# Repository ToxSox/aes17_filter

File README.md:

# AES17 class-D measurement filter

A passive low-pass that sits between a class-D amplifier and an audio analyzer, so that the
amplifier's switching residue never reaches the analyzer's input stage. It is the circuit of
the Audio Precision AUX-0025, on a 158 × 124 mm board in a Hammond 1444-862 aluminium chassis
with every connector in its front long wall, with the 20 kHz knee trimmable, a 20:1 pad that a 4PDT toggle switches on or takes off entirely, and the
AUX-0025's own connectors: female XLR and dual banana in, male XLR out. Designed for a QuantAsylum QA403, usable with
anything that has a 100 kΩ input.

**Status: designed, simulated, generated, not yet built - a prototype, not yet a reference.**
The Gerbers and the JLCPCB files are in `hardware/fab/`, checked against each other by
`hardware/check_release.py`; the first five boards were ordered in November 2026 and have not
been built or measured yet. Everything below the
simulation line is therefore a claim, not a measurement. The design review's
[verification plan](docs/design-review.md#verification-what-makes-it-a-reference) lists what has
to pass before it counts as a reference: the ferrite coils' linearity first, then the ground with
bridged amplifiers, heat, and the stop band.

## Where this comes from

This repository is a fork of Matt Clark's
[aes17_filter_25](https://github.com/mattclarkdotnet/aes17_filter_25) (V2, May 2024), itself a
DIY copy of the AUX-0025, released under the CERN-OHL-W 2.0. The V2 KiCad project, Gerbers,
case cut-outs and dissipation spreadsheet were removed from this tree because they no longer
describe this board; they are intact in the history, on the branch **`v2-mattclark`** (the GitHub proxy of this session refused to push a tag, so it is a branch). The licence
stays the CERN-OHL-W 2.0 (`LICENSE.txt`), and the source location of this derived design is
https://github.com/ToxSox/aes17_filter.

What changed against V2, and why, is argued at length in
[docs/design-review.md](docs/design-review.md), which also takes up the three changes the V2
README had planned (shielded coils: first yes, then no after a second review - see below; a 60 V
goal: no gain; an SMD version: dearer for small runs). In short:

| | V2 (mattclarkdotnet) | this fork | why |
|---|---|---|---|
| Input resistor | 500 Ω 5 W fixed | AP's network: 1 kΩ 3 W ‖ 14 kΩ ‖ (1 kΩ 3 W + 500 Ω trimmer) | the trimmer sets the 20 kHz knee; V2 sits at +0.10 dB and spreads to 0.21 dB with 5 % coils, trimmed boards land at ±0.03 dB whatever the parts |
| Filter values | E24 approximations (330 Ω + 440 pF, 68 Ω, 3.3 kΩ, 22 Ω) | the AUX-0025's own (412 Ω + 2 × 220 pF, 75 Ω, 3.40 kΩ, 24.9 Ω), all E96 | 1-2 dB more in the stop band, nothing to lose |
| Pad | 9 kΩ / 1 kΩ, two poles per leg, hand-wired toggle | 2 × 10 kΩ / 1 kΩ, all 0.1 % / 15 ppm (about 21.8:1), two poles per leg on a 4PDT toggle (gold contacts): in DIRECT the pad is off the output and the filter sees the analyzer alone, as on the AUX-0025. | the QA403 clips at 40 Vrms and loses 20 dB of floor above its +18 dBV range; 20:1 keeps a 2 kW amplifier below both. 0.1 % in every arm because the QA403 subtracts the legs in its analogue input: 1 % arms would let −36 dB of common mode through |
| Connectors | XLR in and out, banana test points | the AUX-0025's: female XLR plus a dual-banana pair and a common in, male XLR out, through the chassis' front wall | one set of cables tests this filter and an AUX-0025 alike; a QA403 hangs on an XLR-to-two-BNC lead |
| Board | 175 × 90 mm, four layers | 158 × 124 mm, four layers, generated from a data file; all connectors on the front long edge; whole ground planes, 0.8 mm clearance, pad and switch at the output connector, one chassis bond at the input | the filter hangs with its connectors towards the operator, as the AUX-0025's front panel; the layout rules are in [hardware/README.md](hardware/README.md#layout-rules-it-follows) |
| Rating | "140 Vrms continuous" | a curve, per leg to ground: 75 Vrms to 15 kHz (the pad), 55 Vrms at 20 kHz (the trimmer's current), 30 Vrms from 30 kHz to 1 MHz (trimmer, then the 0.6 W resistors around the coils); several tones at once (audio over a class-D carrier) share it: the sum of (V / Vmax)² stays at or below 1 | at 20 kHz the shunt capacitors draw current through the input network: V2's single resistor takes 13 W at 140 V, and this build's trimmer reaches its rating at 56 V; above 70 kHz the stop band's current flows in R4 and R6 |
| Coils | Würth 7687480102, unshielded ±5 % | the same Würth 7687480102 | the most linear ferrite coil of the size, and the tightest; the shielded WE-TIS fits the same footprint for comparison |
| Assembly | hand-built | JLCPCB for everything it has in stock (22 parts per board); coils, film capacitors, the two 412 Ω and the Cliff sockets bought locally and soldered by hand | JLCPCB had those only on pre-order (19-21 working days); the trimmer absorbs the tolerances in the frequency response; pairing coils **and** capacitors between the legs to 1 % gains 14 dB of common-mode rejection at 20-100 kHz (one of the two alone 2-4 dB) |

## What is in the tree

| Path | What |
|---|---|
| [docs/design-review.md](docs/design-review.md) | the review of the V2 design against the AUX-0025 and the QA403, the simulation, the pad decision, the build decisions, the bill of materials, grounding with bridged amplifiers, the verification plan, safety |
| [docs/sourcing.md](docs/sourcing.md) | the shopping list with hard specifications, substitutes and open questions |
| [sim/aes17_sim.py](sim/aes17_sim.py) | the AC analysis that produced every number in the review (numpy only) |
| [hardware/](hardware/) | `design.py` (parts and nets as data), `make_pcb.py` (places, routes and checks the board with KiCad's `pcbnew`), `export.py` (Gerbers, BOM, placement), the schematic, the front-wall drilling, and [hardware/README.md](hardware/README.md) with the ordering steps |
| [hardware/fab/](hardware/fab/) | `aes17-filter-gerbers.zip`, `aes17-filter-bom.csv`, `aes17-filter-cpl.csv` for JLCPCB; `aes17-filter-parts.csv` with notes |

## Simulated performance

One leg against ground, 100 kΩ load, relative to 1 kHz; the script prints the full tables.

| | V2 as published | this fork, trimmed |
|---|---|---|
| Passband 20 Hz - 20 kHz | −0.00 / +0.10 dB nominal, up to 0.21 dB spread with ±5 % coils | within ±0.03 dB after trimming, whatever the coils and capacitors |
| −3 dB | 58 kHz | 58 kHz |
| 250 kHz | −53.6 dB | −52.5 dB (two 220 pF instead of 390 pF) |
| 500 kHz | −57.5 dB | −58.4 dB |
| 1 MHz | −69 dB | −70 dB |
| Insertion loss | −0.05 dB | −0.05 dB direct (the pad is switched off) |
| Common mode in the difference, 95 % of boards | - | −74 dB at 50 Hz direct, −52 dB through the pad, −31 dB at 20 kHz; −45 dB with coils and capacitors paired |
| Source noise at the analyzer | −124 dBV direct | −124 dBV direct, −122 dBV through the pad |
| Input resistor at 63 Vrms, 20 kHz | 2.7 W | 1.4 W in each of two |

A real box will land a few decibels short of the stop-band figures: one V1 build measured 45 dB
at 248 kHz against 55 simulated, and the 1 mH coils' self-resonance (1.3 MHz) takes 10-20 dB off
above 2 MHz, where the filter is 80 dB down anyway.

## Bill of materials, per board

The generated list is `hardware/fab/aes17-filter-bom.csv`; this is the same in words. Prices
are LCSC or JLCPCB's global-sourcing quote on 1 November 2026, single quantity.

| Qty | Part | For | Source | ≈ |
|---|---|---|---|---|
| 4 | **Würth WE-TI HV 7687480102**, 1 mH ±5 %, unshielded, 1.0 Ω, 0.8 A, 400 V | L1-L4 | **soldered by hand**, not in the JLCPCB order: Digi-Key (285 in stock at 1.61 € on 1 November 2026); the 120 V 7447480102 is the same coil (JLCPCB C1331132, pre-order). The shielded WE-TIS 7447471102 (C1331105) fits the same footprint and is the comparison for the linearity test; JLCPCB lists it as ±20 %, which the trimmer cannot always reach. Trimmed boards with the ±5 % coil land within 0.032 dB and need R1 between 495 and 534 Ω, inside the network's 483-575 Ω | 2.1 € |
| 4 | UNI-ROYAL MFR03SF1001A10, 1.00 kΩ 1 % 3 W 50 ppm | input network | C58750 | $0.06 |
| 2 | 14.0 kΩ 1 % 0.25 W | input network | C127223 | $0.01 |
| 2 | Bourns 3296W-1-501LF, 500 Ω 25-turn trimmer | 20 kHz knee | C69564 | $0.97 |
| 6 | WIMA FKP2J002201D00HSSD, 220 pF 630 V ±2.5 % | C1, C5, and the bypass pairs C2+C9, C6+C10 (440 pF) | **soldered by hand**, not in the JLCPCB order: Bürklin (also as FKP2J002201D00ESSD, ±1 %, 42D8516); LCSC C5742108 would be pre-order | $0.23 |
| 4 | WIMA FKP2F014701I00JA00, 4.7 nF 250 V ±5 % | C3, C4, C7, C8 | **soldered by hand**, not in the JLCPCB order: Digi-Key (0.67 €); LCSC C20412818 would be pre-order | $0.41 |
| 2 | 412 Ω 1 % **0.6 W**, Vishay MRS25000C4120FCT00 | bypass across L1; carries the stop band above 150 kHz | **soldered by hand**: any 412 Ω 1 % 0.6 W in a 0207 body (Vishay MRS25 / MBB0207, Yageo MF0207) from Digi-Key, Mouser or Bürklin; JLCPCB C1235858 had three in stock | - |
| 2 | 75.0 Ω 1 % 1 W, CCO MF1W | between the stages | C160685 | $0.05 |
| 2 | 3.40 kΩ 1 % **0.6 W**, Vishay MRS25000C3401FCT00 | across L3; carries the current near 100 kHz | C1366835 | - |
| 2 | 24.9 Ω 1 % 0.25 W, Yageo MFR-25FBF52-24R9 | output | C3542579 | $0.03 |
| 4 | TE YR1B10KCC, 10.0 kΩ **0.1 % 15 ppm** 0.25 W | pad, upper arms (2 × 10 kΩ over 1 kΩ, about 21.8:1); the same family as the lower arm | C1364313, in stock | $0.50 |
| 2 | TE YR1B1K0CC, 1.00 kΩ 0.1 % | pad, lower arm | C1364308 | $0.50 |
| 1 | Neutrik NC3FAAH2, female XLR, horizontal PCB | J4, input (pin 2 +, pin 3 −) | C368522, in stock | $0.84-1.80 |
| 1 | Neutrik NC3MAAH, male XLR, horizontal PCB | J5, output (pin 2 +, pin 3 −) | C368463, in stock | $0.79-1.80 |
| 3 | Cliff FCR7350 R / B / G, 4 mm safety sockets, at 19.05 mm for a dual banana plug | J1-J3 | **soldered by hand**, not in the JLCPCB order: Digi-Key, 6.80 € (JLCPCB: pre-order at $11-12) | 7 € |

Not on the board, per board: four screws for the XLR flanges (M3 as the front-wall drawing has
them; check Neutrik's drawing whether the NC3FAAH2 / NC3MAAH flange takes M3 or a 2.9 mm
self-tapping screw), one **4PDT** ON-ON non-shorting toggle with **gold contacts** and a 1/4 in
bushing, such as the APEM 5666CDB (its ten wires go into W1's holes; the switch carries
microamperes, a dry circuit), one Hammond 1444-862 chassis
with its 1434-86 bottom plate and seven 10 mm M3 spacers, the one under the plated hole H5 metal; and once for the bench a lead from the
amplifier terminals to a male XLR plug (or dual banana leads) and an XLR-female-to-two-BNC lead
for the QA403, both of which an AUX-0025 takes as well.

## Ordering and building

[hardware/README.md](hardware/README.md): upload the three files in `hardware/fab/` to JLCPCB,
five boards, all five assembled, Economic. The JLCPCB files hold only parts JLCPCB had in stock, so
the assembly waits for nothing. Everything it had only on pre-order is left out and bought in
Germany (Bürklin, Digi-Key): the ten WIMA capacitors, the four coils, the two 412 Ω and the three
Cliff sockets. They are soldered by hand after assembly, about 55 joints per board; the
capacitors and coils measured and paired between the legs first if an LCR meter is at hand. Then drill the front wall after
`hardware/aes17-filter-frontwall.png`, trim both legs through an amplifier until 20 kHz equals
1 kHz, measure both ratios (PAD about 21.8:1, DIRECT about 1.006:1), and enter them in the
measurement software as the probes' ratios.

## Before connecting it

- **DIRECT passes DC.** A single-supply bridged amplifier idles at half its supply on both
  terminals (+24 V on a 48 V TPA3255); in DIRECT that adds to the signal's peak at the QA403,
  whose absolute maximum is 56 Vpk including DC. With such an amplifier, or an unknown one, use
  PAD, and switch with the amplifier off.
- **It is a class-D pre-filter, not the AES17 low-pass itself**, and it wants a source of a few
  ohms: a line-level output with 50-100 Ω per leg loses 0.3-0.6 dB at 20 kHz through it.
- **The rating is per leg and falls with frequency** (75 / 55 / 30 Vrms, see the table above);
  full-power sweeps above 20 kHz and filterless amplifiers' carriers are what reach it.

## Licence

CERN Open Hardware Licence Version 2 - Weakly Reciprocal, as the original. Copyright of the
original design Matt Clark 2023-2024; the changes described above and in the design review were
made in November 2026 in this repository. If you build or change it, the licence asks that you
keep these notices and make your changes available under the same terms.

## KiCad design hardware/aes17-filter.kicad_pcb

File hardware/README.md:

# AES17 filter board: files and how to order

The passive class-D measurement filter from [docs/design-review.md](../docs/design-review.md),
as a board. Everything here is generated from `design.py`; nothing was drawn by hand, so a
changed value or part is a changed line and a re-run.

| File | What it is |
|---|---|
| `design.py` | every part with value, footprint, LCSC number and note; every net |
| `make_pcb.py` | places and routes the board with KiCad 7's `pcbnew` module, fills the ground planes, runs the DRC; writes `aes17-filter.kicad_pcb` |
| `export.py` | writes `fab/`: the Gerber + drill zip, the JLCPCB bill of materials and placement file, a parts list with notes |
| `make_schematic.py` | draws `aes17-filter-schematic.svg/.png` (schemdraw) |
| `make_frontwall.py` | draws the front wall's drilling and the panel legend, `aes17-filter-frontwall.svg/.png` |
| `check_release.py` | checks that the board, the order files, the source hash and the DRC report belong together; exit code 0 = fit to order |
| `aes17-filter.kicad_pcb` | the board, for KiCad 7 or newer; there is no `.kicad_sch`, the schematic is the drawing |
| `fab/aes17-filter-gerbers.zip` | upload this to JLCPCB |
| `fab/aes17-filter-bom.csv` | upload this as the BOM (Comment, Designator, Footprint, LCSC Part #) |
| `fab/aes17-filter-cpl.csv` | upload this as the placement file (Designator, Mid X, Mid Y, Layer, Rotation) |
| `fab/aes17-filter-parts.csv` | the same parts with values and notes, for ordering anything elsewhere |
| `fab/aes17-filter-schematic.pdf`, `fab/aes17-filter-drc.txt` | the schematic and the DRC report of this release |
| `fab/RELEASE.txt` | title, revision, the source hash printed on the board, and the SHA-256 of every order file |

## The board

158 × 124 mm, four layers, 1.6 mm, in a **Hammond 1444-862** aluminium chassis (203 × 152 × 51 mm,
flat 1 mm walls, closed by the 1434-86 bottom plate). **Every connector is on the front long
edge** and comes through the chassis' front long wall, so the filter hangs with that wall towards
the operator, as the AUX-0025's front panel does. From the left, seen from the front: the female
XLR input (pin 2 +, pin 3 −, pin 1 and shell ground), red and black 4 mm sockets at AP's
19.05 mm for a dual banana plug, the green common, the male XLR output (pin 2 +, pin 3 −), and
the pad toggle, mounted high in the wall straight above the switch. The QA403 is fed through a
self-made lead, XLR female to two BNC males. The first 24 mm behind the front edge are the
connector strip with the switch and the pad block at its right-hand end; the filter is the
100 mm band behind it, the two legs mirror images about its centre line. Layers 2 and 3 are
whole ground planes, broken only by the holes; every track is on layer 1 or 4. The board stands
on seven M3 spacers on the bottom plate (four on the centre line, H5 in the connector strip,
H6 and H7 in the back corners); the XLRs are screwed to the wall, the Cliff sockets held
by the board alone (they have no panel retention; the wall just has a clearance hole for the
Ø11 barrel). The DRC in KiCad 7 reports no errors and no unconnected nets at 0.8 mm clearance;
the warnings are silkscreen over pads and the footprints not being from a library table.

### Layout rules it follows

The board was gone over once more with the usual rules for audio layout. What they changed:

- **Whole ground planes.** Layers 2 and 3 carry nothing but ground. The earlier layout ran the
  two filter outputs on layer 3, which cut slots into the plane right under the output tracks
  on layer 4; those tracks lost their return path exactly where the analyzer's signal ran.
- **Clearance for the voltage.** Everything from the input up to OUT (in the direct position)
  carries the amplifier's voltage: laid out for 120 V peak (85 Vrms per leg, above the 75 Vrms rating). IPC-2221B asks 0.8 mm
  between bare pads at 101-300 V; the board had 0.3 mm and now keeps 0.8 mm everywhere. The
  male XLR's lands on pins 1 and 2 are 3.0 mm instead of Neutrik's 3.4 mm for the same reason.
- **The pad and the switch at the output connector.** The two pads now stand side by side right
  behind the switch, identical copies, so they share a temperature and their ratios track. The
  4PDT toggle sits in the wall straight above W1, ten solder holes, and its wires drop about
  15 mm into them; before, they ran 75 mm through the box to a header in the middle of the
  board. W1's holes run in the order the nets leave the pad block (OUT, F, F, PT, PAD), the +
  leg's row on top and the − leg's on the bottom, so no track crosses another; the − leg's tracks
  come down between the + row's holes, 5.08 mm apart for exactly that.
- **Long runs only at low impedance.** The negative leg ends at the back of the board, so one
  track has to come forward. It is now the filter output F_N, behind 24.9 Ω, the lowest
  impedance in the chain, and it runs alone through empty board. Before, the output pair came
  back to the middle of the board, and in the pad position OUT sits behind 950 Ω, where 1 pF of
  stray capacitance from the input side is already −50 dB at 500 kHz.
- **Pairs kept together.** IN+ and IN− run on top of each other (layer 1 over layer 4) from the
  connectors to where the legs part; OUT+ and OUT− run side by side, 1 mm apart, from W1 to the
  XLR. Before, the negative input went round the board's left edge and the two outputs ran 10 mm
  apart.
- **More distance between the stages.** The second coil of each leg is 38 mm from the first
  instead of 32 mm. Coupling between two drum cores falls with the cube of the distance, so
  L1 → L2, the one path that bypasses the filter, is about 4.5 dB weaker.
- **One chassis bond, where the cables come in.** H5 is a plated hole on ground in the
  connector strip, next to the input XLR: with a metal spacer it ties the ground plane to the
  bottom plate and so to the chassis, and cable shield currents go to the chassis there instead
  of crossing the filter. The other six holes are plain.

What stayed as it was, because it was right: the two legs mirror images, so each sees the same
parasitics; the shunt capacitors' grounds meeting in the middle of the board, so the
differential residue current takes a short path between the legs; polypropylene capacitors and
metal-film resistors throughout; the hot 3 W input resistors well away from the polypropylene
capacitors (FKP2 is rated to 100 °C).

### Silkscreen

Top: every part with its name and value in the notation that survives a lost dot (R1 1k 3W,
R7 24R9, C3 4n7, L1 1mH), the pad block with a legend under each pad, each leg's signal flow
along its outer edge (input network, stage 1, stage 2, pad), a high-voltage warning beside the
inputs, W1's ten holes labelled for the toggle wires (+OUT, +F, +F, +PT, +PAD and the same with −), and the title
"AES17 filter rev A" with date, licence and source location (the CERN-OHL-W asks for the source
location on the product where practicable). Bottom, readable from below: a crib sheet with the
connector pin-outs and the QA403 lead, the switch wiring, the trim procedure and
the voltage limits. Both sides carry "src" and the source hash, the first seven digits of the
SHA-256 of `design.py` and `make_pcb.py`, the same as in `fab/RELEASE.txt`. Two ground loops,
TP1 and TP2, sit between the stages for a scope probe's ground spring. Title, revision and date
are three constants at the top of `design.py`.

## Ordering at JLCPCB

0. **Check the release.** `python3 hardware/check_release.py` must end with "fit to order".
   Order from a commit, not from a working copy, and keep its source hash (in `fab/RELEASE.txt`
   and printed on both sides of the board, "src ...") with the order: a board in the hand is
   then matched to its files without guessing.
1. **PCB.** Upload `fab/aes17-filter-gerbers.zip`. Four layers, 1.6 mm, any colour, 1 oz copper,
   HASL or ENIG as you like, five pieces (the minimum). The stack-up JLCPCB offers for four
   layers (JLC04161H-7628 or similar) is fine; nothing here depends on impedance.
2. **Assembly.** Tick assembly, **five boards** (all of them: two for this bench, two for a
   colleague's, one spare; JLCPCB's minimum is two), top side only, Economic. Upload
   `fab/aes17-filter-bom.csv` and `fab/aes17-filter-cpl.csv`. All parts are through-hole;
   JLCPCB hand-solders those ($3.58 per order plus $0.0164 per joint, one extra day).
3. **Parts review.** In the parts page every line with an LCSC number resolves on its own,
   because the files hold only parts JLCPCB had in stock. **Left out, to be bought locally and
   soldered by hand:** the coils L1-L4 (Würth 7687480102, Digi-Key; at JLCPCB only the
   7447480102, C1331132, on pre-order), the 412 Ω R4/R14, the Cliff sockets J1-J3 and the film
   capacitors C1-C10. The shielded
   WE-TIS 7447471102, C1331105, fits the same footprint; it was the coil of the first draw of
   rev A and is now only the comparison for the linearity test (JLCPCB lists it as ±20 %, which
   the trimmer cannot always reach). The 412 Ω 0.6 W had three pieces in stock at JLCPCB
   (C1235858) on 2 November 2026; any 412 Ω 1 % 0.6 W in a 0207 body does. The
   BOM file is plain ASCII on purpose: JLCPCB's import reads "Würth" as "W眉rth". The ten WIMA film capacitors (C1-C10) are **not in the BOM and the placement file**: JLCPCB has them only on pre-order (19-21 working days, quoted on 3 November 2026), so they are bought locally and soldered by hand. The Cliff sockets would be **pre-order** too: JLCPCB
   buys them after payment, quotes the final price within 48 hours, and they take nine to
   twenty business days to arrive; connectors carry a $20 inspection fee per type, so the three
   Cliff colours cost $60 in inspection alone. So they are **left out of the assembly** (they
   are not in the files), bought at Digi-Key (6.80 € each against $11-12 pre-order) and solder the three per board yourself - one
   pin and four pegs each.
4. **Every line has an LCSC number.** The pad's upper arms (R8, R9, R18, R19) are TE YR1B10KCC,
   10.0 kΩ 0.1 % 15 ppm, C1364313 (2 397 in stock on 2 November 2026), the same family as the
   1.00 kΩ lower arm; a 0207 body on the 15.24 mm pitch. R6/R16 are the Vishay MRS25 3.40 kΩ
   0.6 W, C1366835 (125 in stock).
5. **W1 is not a part.** It is ten plated holes for the toggle's wires and is not in the BOM or
   the placement file; the 4PDT toggle is bought separately (RS, Mouser) and wired by hand.
6. After the order: the five boards arrive assembled. Nothing else is needed from JLCPCB.

### What JLCPCB's BOM tool quoted on 1 November 2026

For an assembly of five boards (quantities include JLCPCB's attrition allowance), in euros:

| Line | Qty | Total | Per piece | Status |
|---|---|---|---|---|
| TE 5227161-7 BNC (C591726) | 20 | 99.63 | 4.98 | in stock; no longer on the board - the XLR output replaced the BNCs |
| Cliff FCR7350R / B / G (C6041087 / C6555263 / C6041085) | 5 each | 58.13 / 58.13 / 50.32 | 11.6 / 11.6 / 10.1 | **shortage: pre-order**, plus the connector inspection fee per type |
| WIMA 220 pF 630 V ±2.5 % (C5742108) | 30 | 7.19 | 0.24 | shortage: pre-order, 19 working days; now soldered by hand instead |
| WIMA 4.7 nF 250 V (C20412818) | 25 | 10.70 | 0.43 | shortage: pre-order, 21 working days; now soldered by hand instead |
| Bourns 3296W-1-501LF (C69564) | 10 | 6.75 | 0.67 | in stock |
| TE YR1B1K0CC 0.1 % (C1364308) | 10 | 3.57 | 0.36 | in stock |
| UNI-ROYAL 1 kΩ 3 W (C58750) | 21 | 1.04 | 0.05 | in stock |
| UNI-ROYAL 10 kΩ 1 W (C58714) | 21 | 0.51 | 0.02 | in stock; replaced by TE YR1B10KCC 0.1 % (C1364313, about 0.50 € each) |
| 75 Ω 1 W (C160685) | 11 | 0.47 | 0.04 | in stock |
| 14 k, 412, 3.4 k, 24.9 (C127223, C3558411, C3517441, C3542579) | 11-15 each | 0.15 / 0.06 / 0.17 / 0.36 | 0.01-0.02 | in stock; the 412 and 3.4 k are now 0.6 W Vishay MRS25 (C1235858, C1366835), not yet quoted |
| Würth 7447471102 coils | 20 | about 58 | 2.9 | "Vorbestellen" → global sourcing; replaced by the unshielded 7447480102 (C1331132, 2.14 €) |

About 356 € of parts for five assembled boards, 71 € per board, of which the three Cliff sockets
are 33 € and the four BNCs 20 € (the BNCs have since left the board). The Cliff sockets are the line to take out of the assembly:
pre-order at 11 € each plus the inspection fee, against 6.80 € at Digi-Key for a part with one
pin and four pegs to solder. That quote still holds the BNCs, the Cliff sockets, the film
capacitors and the coils, none of which is in the JLCPCB files any more; what JLCPCB fits now is
the resistors, the trimmers and the two XLRs, so the parts bill it shows at ordering is well
below it. The stock of all ten lines covered five boards on 3 November 2026; the tightest were
C58750 (1 kΩ 3 W, 153 for 20) and C1366835 (3.40 kΩ, 125 for 10).

## Shopping list, bought locally (five boards)

JLCPCB fits the 22 parts per board it had in stock. Everything else is bought locally; the
quantities are for all five boards and include what pairing the legs needs (see "Building the
boards", step 1). Pair from **one pool for all five**: any matched pair can go on any board.
**Why 24 of a ±5 % part for 20 places:** ten pairs within 1 % are wanted; the chance of finding
them is 21 % from 20 parts, 93 % from 22 and 100 % from 24 if the values spread evenly over the
tolerance, and 42 / 98 / 100 % for a typical reel, whose spread is narrower (simulated,
tolerance = 3σ). Two more cover a bent lead and give the winding-sense test its sender coil.
For a single board it would be 8 for 4 places (98 %), for two boards 12 for 8: the bigger the
pool, the smaller the surplus per board.

**On the board, soldered by hand:**

| Buy | Fitted | Part | Pairing | Where |
|---|---|---|---|---|
| 26 | 20 | **Würth 7687480102**, 1 mH ±5 %, unshielded drum core (L1-L4) | ten pairs, L1/L3 and L2/L4 per board, from 24 | Digi-Key |
| 26 | 20 | **WIMA FKP2F014701I00JA00**, 4.7 nF 250 V ±5 % (C3, C4, C7, C8) | ten pairs, C3/C7 and C4/C8 per board, from 24 | Digi-Key |
| 33 | 30 | **WIMA FKP2J002201D00ESSD**, 220 pF 630 V **±1 %** (C1, C2, C5, C6, C9, C10) | two ±1 % parts differ by 2 % at most, which is what the simulation counts as paired; measure and sort anyway: the closest two as C1/C5, then C2 + C9 against C6 + C10 | Bürklin 42D8516 |
| (40) | (30) | or the ±2.5 % FKP2J002201D00HSSD, if the ±1 % is not to be had | then pairing matters: 40 to choose from | Digi-Key, Bürklin |
| 12 | 10 | **412 Ω 1 % 0.6 W**, Vishay MRS25000C4120FCT00 or any 0207 body (R4, R14) | none needed | Digi-Key, Mouser, Bürklin |
| 5 each | 5 each | **Cliff FCR7350R, FCR7350B, FCR7350G**, red, black, green (J1-J3) | - | Digi-Key, Farnell |

**For pairing and the verification tests, not on the board** (one set does all five boards, if
one person pairs, trims and tests them; that is also how all five come out alike):

| Buy | Part | For |
|---|---|---|
| 1 each | 100 Ω, 6.8 kΩ, 47 kΩ, 1 %, 0.25 W | the series resistor when pairing with the QA403: coils, 4.7 nF, 220 pF |
| 2 + 1 | 10 kΩ and 1 kΩ, 1 %, **3 W or more**, metal film (the UNI-ROYAL MFR03S on the board, or a Vishay PR03) | test 4's reference divider, 2 × 10 k over 1 k as the pad: at 75 Vrms it runs at about 4 % of its rating, so it adds no self-heating distortion of its own |
| 1 | 1 Ω, 1 % | test 5's current shunt in the green lead |
| 4, optional | Würth WE-TIS 7447471102, shielded | test 4's comparison, one board's worth (availability outside JLCPCB not checked) |

Plus the box, the toggle and the leads in the next table.

## What is not on the board

| Qty for five boards | Part | Where |
|---|---|---|
| 20 | screws for the XLR flanges: M3 × 8 and nuts if the flange holes are through-holes, else 2.9 mm self-tapping (Neutrik's drawing of the NC3FAAH2 / NC3MAAH decides; not checked) | any |
| 2 | a cable from the amplifier's terminals to a male XLR plug (pin 2 +, pin 3 −), or dual banana leads - the same cable then feeds an AUX-0025; one per bench | self-made |
| 2 | an XLR-female-to-two-BNC-male lead to the QA403: pin 2 to L+ centre, pin 3 to L− centre, pin 1 to both BNC shells; about 30 cm, both legs equal; one per bench | self-made (Neutrik NC3FXX, two BNC plugs, two pieces of RG58 or RG174) |
| 5 | **4PDT** toggle, ON-ON, non-shorting, **gold contacts**, panel mount, 1/4 in bushing, solder lugs; best with a locking lever | APEM 5666CDB or another 4PDT with gold contacts; the switch carries microamperes at 100 kΩ, a dry circuit, so standard silver contacts (a plain Knitter MTA 206, for one) are not suitable. Gold contacts are rated to switch only 0.4 VA at 20 V: they carry the full voltage closed, but are switched with the amplifier off |
| 5 | insulating sheet, 0.25 mm polyester or fish paper, cut to the bottom plate around the spacers | any |
| 5 | Hammond 1444-862 chassis and 1434-86 bottom plate | Digi-Key, Mouser, Reichelt; about 20 € and 11 € |
| 35 | M3 spacers, 10 mm, and M3 screws, for the board on the bottom plate (seven per board); the one under H5 metal, with a star washer on the bottom plate | any |
| | wire for the toggle: ten pieces per board of about 25 mm, 0.25 mm² stranded, into W1's holes | |

## Building the boards

1. Check the assembled board against `fab/aes17-filter-parts.csv`.
   Then solder what JLCPCB leaves out, per board: the 412 Ω 0.6 W in R4 and R14; the coils,
   L1/L2 (+ leg) and L3/L4 (− leg), all four with the same winding sense (see below); 220 pF in C1, C2, C9 (+) and C5, C6, C10 (−),
   4.7 nF in C3, C4 (+) and C7, C8 (−); and the Cliff sockets, red J1, black J2, green J3. Before
   soldering, **measure coils and capacitors and give the two legs the closest pairs** (L1/L3,
   L2/L4, C1/C5, C2+C9 / C6+C10, C3/C7, C4/C8); the polypropylene parts have no polarity. For
   the frequency response the trimmer takes care of the spread, but not for the legs' phase:
   pairing **both** coils and capacitors to 1 % moves the common mode in the difference from
   −31 to −45 dB at 20 kHz and from −14 to −29 dB at 100 kHz (simulation, 95 % of boards);
   pairing only one of the two gains 2-4 dB, because the other still sets the phase.

   **Pairing without an LCR meter**, with the QA403: its output through a series resistor
   into the part, the part's other end to ground; the left input across the part, the right
   input on the output. Sweep once to find where the left reads 3 dB below the right, then
   read every part of that value at that frequency: 1 % in value is about 0.04 dB there. The
   resistor sets the frequency: 6.8 kΩ for the 4.7 nF (about 5 kHz), 47 kΩ for the 220 pF
   (about 10 kHz with the lead's capacitance), 100 Ω for the 1 mH coils (about 16 kHz). Keep
   the leads and the part's position the same for every part of one value; only the
   differences count.

   **Winding sense of the coils.** For the filter either way round works, but an unshielded
   drum core picks up stray magnetic fields (a mains transformer, a load bank), and the
   aluminium box does not screen 50 Hz. A field that reaches both legs alike then appears as
   common mode, which the QA403 rejects, only if L1 and L3 (and L2 and L4) are the same way
   round; Würth does not mark the start of the winding. To find it with the QA403 before
   soldering: QA403 output, 1 kHz at about 1 V, into one coil (the "sender") through 100 Ω;
   stand each other coil on top of it, axis on axis and always leads up, its leads to the left
   input, and read the phase against the output: about +90° or −90° (the induced voltage leads
   the current). Mark the lead that gives +90° on the left input's centre pin and put it in the
   square pad on all four. Then test the sender itself the same way, with a marked coil as
   the sender.
2. Drill the front wall after `aes17-filter-frontwall.png`; the hole table is at the end of this
   file. Easiest and safest: drill the seven spacer holes in the bottom plate, stand the board on
   its spacers, put the chassis over it, and mark the connector centres through from inside.
3. Fit the board on the bottom plate, put the chassis over it, screw the XLR flanges to the
   wall, fit the toggle.
4. Wire the 4PDT toggle into W1, straight below it, by the silkscreen labels: two poles per
   leg, the + leg to the back row, the − leg to the front row. Decide which lever position is
   PAD and call the throw lugs on that side "PAD side", the others "DIR side"; then per leg
   - pole a: common → PT, PAD side → F, DIR side not connected
   - pole b: common → OUT, PAD side → PAD, DIR side → the other F
   Check with an ohmmeter between the output XLR's pin 2 (then pin 3) and pin 1, inputs open:
   about 1.0 kΩ in PAD (the pad's 1 kΩ leg), open in DIRECT (the pad is off). And from the red
   (then black) input to the green: about 21 kΩ in PAD, open in DIRECT. Mark the positions on the
   front.
5. Lay the insulating sheet on the bottom plate before the board goes in; use a metal spacer
   under H5 and plastic or metal under the rest (only H5 is plated). Set the trimmers (step 6)
   with a few volts from the amplifier: the trim does not depend on the level, and the box is
   open while you turn them.
6. Work through the [verification plan](../docs/design-review.md#verification-what-makes-it-a-reference):
   trim both legs through an amplifier until 20 kHz equals 1 kHz, the pad ratio over frequency
   into the measurement software's probe settings, then the ferrite, ground, heat and stop-band tests before the
   filter is used as a reference. Connect the green socket to the amplifier's ground in use.

## Regenerating

```
python3 hardware/make_pcb.py        # board + DRC report (needs KiCad 7 with pcbnew for Python)
python3 hardware/make_schematic.py  # schematic, also fab/…-schematic.pdf (pip install schemdraw)
python3 hardware/export.py          # fab/ and fab/RELEASE.txt (needs kicad-cli; after the schematic)
python3 hardware/make_frontwall.py  # front wall drilling (matplotlib)
python3 hardware/check_release.py   # do the files belong together?
```

Run `make_schematic.py` before `export.py`: the schematic PDF is one of the files the release
manifest hashes.

## Front wall holes

See `aes17-filter-frontwall.png`; the table below is printed by `make_frontwall.py`. In blue the
drawing also carries the legend for the panel: the rating per leg at the inputs, "GND to the
amplifier ground", the switch positions and DIRECT's 40 Vrms limit. The wall is
the front long wall of the Hammond 1444-862, seen from outside, x from its left end, y from its
bottom edge (which rests on the 1434-86 bottom plate).

| Hole | Ø mm | x | y |
|---|---|---|---|
| XLR IN (female), Neutrik NC3FAAH2 | 22.5 | 40.6 | 24.1 |
| its two M3 screws, upper left and lower right | 3.2 | 30.7 / 50.5 | 34.0 / 14.2 |
| 4 mm IN + (red) | 11.5 | 67.6 | 17.9 |
| 4 mm IN − (black), 19.05 mm from the red one | 11.5 | 86.6 | 17.9 |
| 4 mm GND (green) | 11.5 | 107.6 | 17.9 |
| XLR OUT (male), Neutrik NC3MAAH | 22.5 | 134.6 | 24.1 |
| its two M3 screws, upper left and lower right | 3.2 | 124.7 / 144.5 | 34.0 / 14.2 |
| pad toggle, 1/4 in bushing | 6.4 | 158.6 | 35.6 |

The heights assume the board on **10 mm M3 spacers** on the bottom plate, so its top surface is
11.6 mm above the wall's bottom edge; the Cliff socket axis is 6.3 mm above the board, the XLR
axis 12.5 mm, the toggle's 24 mm (so that the 4PDT's body, about 13 × 17 mm and 20 mm deep with its lugs, clears the board). **The XLR axis height is read off Neutrik's front view, not a dimensioned value:
fit the board on its spacers, hold the undrilled wall against the connector fronts and mark
through before drilling.** The board's front edge sits 3.3 mm behind the wall's inner face, so
the XLR flanges and the shoulders of the 4 mm sockets lie against the wall. Cliff does not
specify a panel hole for the S16N-PC; Ø11.5 clears its Ø11.0 barrel. Neutrik asks for a hole of
at least Ø22 and two Ø3.2 screw holes 19.8 mm apart on the diagonal.

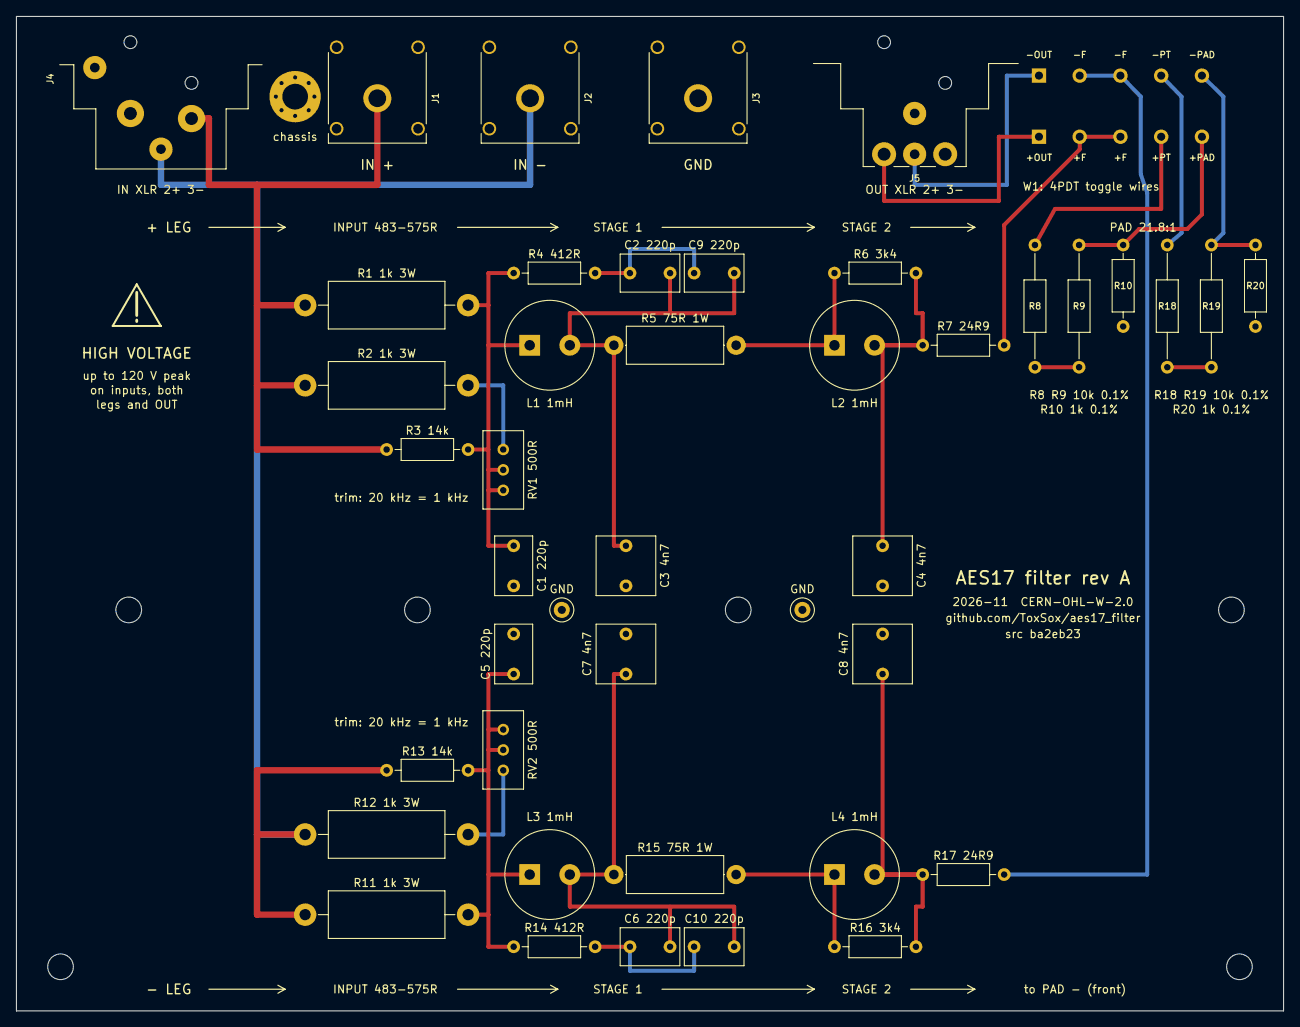
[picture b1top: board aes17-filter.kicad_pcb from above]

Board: 4 copper layers, 158.0 x 124.0 mm, 51 parts (0 on the bottom side), 25 nets.

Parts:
C1, C2, C5, C6, C9, C10: 220p; C_Rect_L7.2mm_W4.5mm_P5.00mm_FKS2_FKP2_MKS2_MKP2
C3, C4, C7, C8: 4.7n; C_Rect_L7.2mm_W7.2mm_P5.00mm_FKS2_FKP2_MKS2_MKP2
H1, H2, H3, H4, H6, H7: M3; MountingHole_3.2mm_M3
H5: M3 GND; MountingHole_3.2mm_M3_Pad_Via
J1: IN +; Banana_Cliff_FCR7350R_S16N-PC_Horizontal
J2: IN -; Banana_Cliff_FCR7350B_S16N-PC_Horizontal
J3: GND; Banana_Cliff_FCR7350G_S16N-PC_Horizontal
J4: IN XLR; Jack_XLR_Neutrik_NC3FAAH2_Horizontal
J5: OUT XLR; Jack_XLR_Neutrik_NC3MAAH_Horizontal
L1, L2, L3, L4: 1mH; L_Radial_D11.5mm_P5.00mm
R1, R2, R11, R12: 1.00k 3W; R_Axial_DIN0614_L14.3mm_D5.7mm_P20.32mm_Horizontal
R3, R13: 14.0k; R_Axial_DIN0207_L6.3mm_D2.5mm_P10.16mm_Horizontal
R4, R14: 412R; R_Axial_DIN0207_L6.3mm_D2.5mm_P10.16mm_Horizontal
R5, R15: 75.0R 1W; R_Axial_DIN0414_L11.9mm_D4.5mm_P15.24mm_Horizontal
R6, R16: 3.40k; R_Axial_DIN0207_L6.3mm_D2.5mm_P10.16mm_Horizontal
R7, R17: 24.9R; R_Axial_DIN0207_L6.3mm_D2.5mm_P10.16mm_Horizontal
R8, R9, R18, R19: 10.0k 0.1%; R_Axial_DIN0207_L6.3mm_D2.5mm_P15.24mm_Horizontal
R10, R20: 1.00k 0.1%; R_Axial_DIN0207_L6.3mm_D2.5mm_P10.16mm_Horizontal
RV1, RV2: 500R; Potentiometer_Bourns_3296W_Vertical
TP1, TP2: GND; TestPoint_Loop_D2.50mm_Drill1.0mm
W1: 4PDT wires; Wire_Field_4PDT

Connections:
A_N: C5.1, L3.1, R11.2, R13.2, R14.1, RV2.2, RV2.3
A_P: C1.1, L1.1, R1.2, R3.2, R4.1, RV1.2, RV1.3
B_N: C6.2, C7.1, C10.2, L3.2, R15.1
B_P: C2.2, C3.1, C9.2, L1.2, R5.1
D_N: L4.1, R15.2, R16.1
D_P: L2.1, R5.2, R6.1
E_N: C8.1, L4.2, R16.2, R17.1
E_P: C4.1, L2.2, R6.2, R7.1
F_N: R17.2, W1.7, W1.8
F_P: R7.2, W1.2, W1.3
GND: C1.2, C3.2, C4.2, C5.2, C7.2, C8.2, H5.1, J3.1, J4.1, J4.G, J5.1, J5.G, R10.2, R20.2, TP1.1, TP2.1
IN_N: J2.1, J4.3, R11.1, R12.1, R13.1
IN_P: J1.1, J4.2, R1.1, R2.1, R3.1
M_N: R18.2, R19.1
M_P: R8.2, R9.1
OUT_N: J5.3, W1.6
OUT_P: J5.2, W1.1
PAD_N: R19.2, R20.1, W1.10
PAD_P: R9.2, R10.1, W1.5
PT_N: R18.1, W1.9
PT_P: R8.1, W1.4
T_N: R12.2, RV2.1
T_P: R2.2, RV1.1
X_N: C6.1, C10.1, R14.2
X_P: C2.1, C9.1, R4.2

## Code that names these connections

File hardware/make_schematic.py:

#!/usr/bin/env python3
"""Draws the filter schematic with schemdraw (pip install schemdraw):

    python3 make_schematic.py      # in this directory

writes aes17-filter-schematic.svg and .png next to this file. One leg is drawn in full; the
other is identical and shares only ground and the 4PDT toggle. Every element is placed
by coordinates so the drawing stays legible whatever schemdraw's defaults are.

Every value and every W1 hole number is read from design.py, and the drawing carries the
SHA-256 of design.py (design_hash below), which check_release.py compares, so the schematic in a
release cannot describe other parts than the board.
"""
import hashlib
import os
import sys

import schemdraw
import schemdraw.elements as elm

HERE = os.path.dirname(os.path.abspath(__file__))
sys.path.insert(0, HERE)
import design  # noqa: E402

VALUE = {ref: value for ref, value, *_ in design.PARTS}
PIN = {}
for _ref, _v, _f, _l, _n, _pins in design.PARTS:
    for _pad, _net in _pins:
        PIN.setdefault((_ref, _net), []).append(_pad)


def w1(net):
    """'W1-2/3': the hole(s) of the toggle's wire field on that net."""
    return 'W1-' + '/'.join(str(p) for p in PIN['W1', net])


def design_hash():
    """The first seven hex digits of the SHA-256 of design.py, printed on the drawing."""
    with open(os.path.join(HERE, 'design.py'), 'rb') as f:
        return hashlib.sha256(f.read()).hexdigest()[:7]


def v(ref):
    """'R1  1.00k 3W': the reference and its value from design.py."""
    return f'{ref}  {VALUE[ref]}'


def R(d, a, b, label, loc='top'):
    d += elm.Resistor().at(a).to(b).label(label, loc=loc, fontsize=9)


def C(d, a, b, label, loc='bottom'):
    d += elm.Capacitor().at(a).to(b).label(label, loc=loc, fontsize=9)


def L(d, a, b, label):
    d += elm.Inductor2(loops=4).at(a).to(b).label(label, loc='bottom', fontsize=9)


def line(d, *pts):
    for a, b in zip(pts, pts[1:]):
        d += elm.Line().at(a).to(b)


def dot(d, p, label=None, loc='top', open_=False):
    e = elm.Dot(open=open_).at(p)
    if label:
        e = e.label(label, loc=loc, fontsize=9)
    d += e


def gnd(d, p):
    d += elm.Ground().at(p)


with schemdraw.Drawing(show=False) as d:
    d.config(fontsize=9)
    # ---- input --------------------------------------------------------------------------
    dot(d, (0, 0), 'IN +   J4 XLR pin 2 and J1 (red 4 mm) in parallel', loc='left', open_=True)
    line(d, (0, 0), (1, 0)); dot(d, (1, 0))
    line(d, (1, 2), (1, -2))
    R(d, (1, 2), (6, 2), v('R1'))
    R(d, (1, 0), (3.4, 0), v('R2'), loc='bottom')
    d += elm.Potentiometer().at((3.4, 0)).to((6, 0)).label(v('RV1') + '\n20 kHz trim', loc='bottom', fontsize=9)
    R(d, (1, -2), (6, -2), v('R3'), loc='bottom')
    line(d, (6, 2), (6, -2)); dot(d, (6, 0), 'A')
    # ---- first stage --------------------------------------------------------------------
    line(d, (6, 0), (7.5, 0)); dot(d, (7.5, 0))
    C(d, (7.5, 0), (7.5, -2.2), v('C1').replace('  ', '\n')); gnd(d, (7.5, -2.2))
    L(d, (7.5, 0), (10.5, 0), v('L1') + '  ' + design.MPN['L1'])
    line(d, (7.5, 0), (7.5, 2)); R(d, (7.5, 2), (9, 2), v('R4').replace('  ', '\n')); C(d, (9, 2), (10.5, 2), f'C2 || C9\n{VALUE["C2"]} + {VALUE["C9"]}', loc='top'); line(d, (10.5, 2), (10.5, 0))
    dot(d, (10.5, 0), 'B')
    C(d, (10.5, 0), (10.5, -2.2), v('C3').replace('  ', '\n')); gnd(d, (10.5, -2.2))
    # ---- second stage -------------------------------------------------------------------
    R(d, (10.5, 0), (13.5, 0), v('R5'))
    dot(d, (13.5, 0), 'D')
    L(d, (13.5, 0), (16.5, 0), v('L2'))
    line(d, (13.5, 0), (13.5, 2)); R(d, (13.5, 2), (16.5, 2), v('R6')); line(d, (16.5, 2), (16.5, 0))
    dot(d, (16.5, 0), 'E')
    C(d, (16.5, 0), (16.5, -2.2), v('C4').replace('  ', '\n')); gnd(d, (16.5, -2.2))
    R(d, (16.5, 0), (19.5, 0), v('R7'))
    dot(d, (19.5, 0), 'F', loc='top')
    # ---- pad, fed through pole a of the toggle: on F in PAD only --------------------------
    line(d, (19.5, 0), (19.5, -0.7)); dot(d, (19.5, -0.7), None, open_=True)          # PAD throw = F
    dot(d, (20.6, -0.7), 'n.c.', loc='right', open_=True)                              # DIRECT throw
    dot(d, (19.5, -1.9), None, open_=True)                                             # common = PT
    d += elm.Line().at((19.5, -1.9)).to((19.55, -0.85)).linewidth(2)                  # blade, PAD position
    d += elm.Label().at((19.9, -1.55)).label(f"S1a (pad feed): COM {w1('PT_P')}, PAD {w1('F_P')}", fontsize=8, halign='left')
    line(d, (19.5, -1.9), (19.5, -2.5))
    R(d, (19.5, -2.5), (22.5, -2.5), v('R8'), loc='bottom')
    R(d, (22.5, -2.5), (25.5, -2.5), v('R9'), loc='bottom')
    dot(d, (25.5, -2.5), 'PAD  (about 21.8:1 tap)')
    R(d, (25.5, -2.5), (25.5, -5), v('R10'), loc='bottom'); gnd(d, (25.5, -5))
    # ---- pole b of the toggle: the output takes the tap or F ------------------------------
    line(d, (19.5, 0), (28, 0)); dot(d, (28, 0), f"DIRECT   {w1('F_P')}", loc='top', open_=True)
    line(d, (25.5, -2.5), (28, -2.5)); dot(d, (28, -2.5), f"PAD   {w1('PAD_P')}", loc='bottom', open_=True)
    dot(d, (30, -1.25), None, open_=True)
    d += elm.Line().at((30, -1.25)).to((28.25, -2.4)).linewidth(2)     # the blade, drawn in the PAD position
    line(d, (30, -1.25), (32, -1.25)); dot(d, (32, -1.25), f"OUT +   S1b COM {w1('OUT_P')}   to J5 XLR pin 2", loc='right', open_=True)
    # ---- notes ---------------------------------------------------------------------------
    d += elm.Label().at((0, -7.2)).label(
        f"Negative leg, IN - (J4 XLR pin 3 / J2 black) to OUT - (J5 XLR pin 3): identical; R11-R20, RV2, C5-C10, L3, L4; its switch is poles c and d of S1: OUT {w1('OUT_N')}, F {w1('F_N')}, PT {w1('PT_N')}, PAD {w1('PAD_N')}.\n"
        'XLR pin 1 and shell, J3 (green 4 mm), the ground plane and the box: GND = the QA403\'s Audio Common. Connectors as on the AP AUX-0025; the QA403 takes an XLR-to-two-BNC lead.\n'
        'S1: 4PDT ON-ON toggle in the front wall, non-shorting, gold contacts (APEM 5666CDB or similar), its wires soldered into W1; drawn in the PAD position.\n'
        'In DIRECT the pad is off the output: the filter sees the analyzer alone, as the AUX-0025 does (about 1.006:1). In PAD the analyzer sees about 1/22 of the amplifier (measure it);\n'
        'DIRECT is the full voltage, DC included: a single-supply bridged amplifier idles at half its supply on both legs, which adds to the peak the QA403 sees.\n'
        f'All values from design.py, sha256 {design_hash()}.',
        halign='left', fontsize=8)

    d.save(os.path.join(HERE, 'aes17-filter-schematic.svg'))
    d.save(os.path.join(HERE, 'aes17-filter-schematic.png'), dpi=150)
    d.save(os.path.join(HERE, 'fab', 'aes17-filter-schematic.pdf'))   # the release copy
print('ok')

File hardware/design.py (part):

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PARTS = leg('P', NAMES_P, NETS_P) + leg('N', NAMES_N, NETS_N) + [
    # connectors, input end (x = 0), the AUX-0025's set: female XLR (pin 2 +, pin 3 -, pin 1 and
    # shell ground) and a dual-banana pair at 19.05 mm (AP's 3/4 in), plus a common terminal
    ('J4', 'IN XLR', 'XLR_F',   'C368522', 'Neutrik NC3FAAH2, pin 2 = +, pin 3 = -, pin 1 and G = ground', [(1, 'GND'), (2, 'IN_P'), (3, 'IN_N'), ('G', 'GND')]),
    ('J1', 'IN +',  'BANANA_R', 'C6041087', 'Cliff FCR7350R red, amplifier +; with J2 at 19.05 mm for a dual banana plug; soldered by hand (Digi-Key)', [(1, 'IN_P')]),
    ('J2', 'IN -',  'BANANA_B', 'C6555263', 'Cliff FCR7350B black, amplifier -; soldered by hand (Digi-Key)',         [(1, 'IN_N')]),
    ('J3', 'GND',   'BANANA_G', 'C6041085', 'Cliff FCR7350G green, common / chassis; soldered by hand (Digi-Key)',    [(1, 'GND')]),
    # connectors, output end (x = 158): the AUX-0025's male XLR; the QA403 takes an XLR-to-two-BNC lead
    ('J5', 'OUT XLR', 'XLR_M',  'C368463', 'Neutrik NC3MAAH, pin 2 = +, pin 3 = -, pin 1 and G = ground', [(1, 'GND'), (2, 'OUT_P'), (3, 'OUT_N'), ('G', 'GND')]),
    # the pad switch: a 4PDT ON-ON toggle in the front wall (gold contacts, non-shorting), its
    # wires soldered into W1, ten holes straight below it. Per leg two poles:
    #   pole a, pad feed:  common -> PT,  PAD throw -> F,   DIRECT throw not connected
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

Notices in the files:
hardware/aes17-filter.kicad_pcb:
2026-11  CERN-OHL-W-2.0
